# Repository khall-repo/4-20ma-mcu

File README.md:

# 4-20ma-mcu
0-5v to 4-20mA conversion using ATTINY84 and a LM324

This project is just to edify myself on making a PCB and having it fabricated.

Needed to build this project:<br/>
gcc-avr  - GNU C compiler (cross compiler for avr)<br/>
avr-libc - Standard C library for Atmel AVR development<br/>
avrdude  - software for programming Atmel AVR microcontrollers<br/>

Make:<br/>
make           - will compile and link only.<br/>
make flash     - will compile, link, and then program flash memory.<br/>
make fuse      - will compile, link, and then program fuses.<br/>
make program   - will compile, link, program fuses, and then program flash memory.<br/>

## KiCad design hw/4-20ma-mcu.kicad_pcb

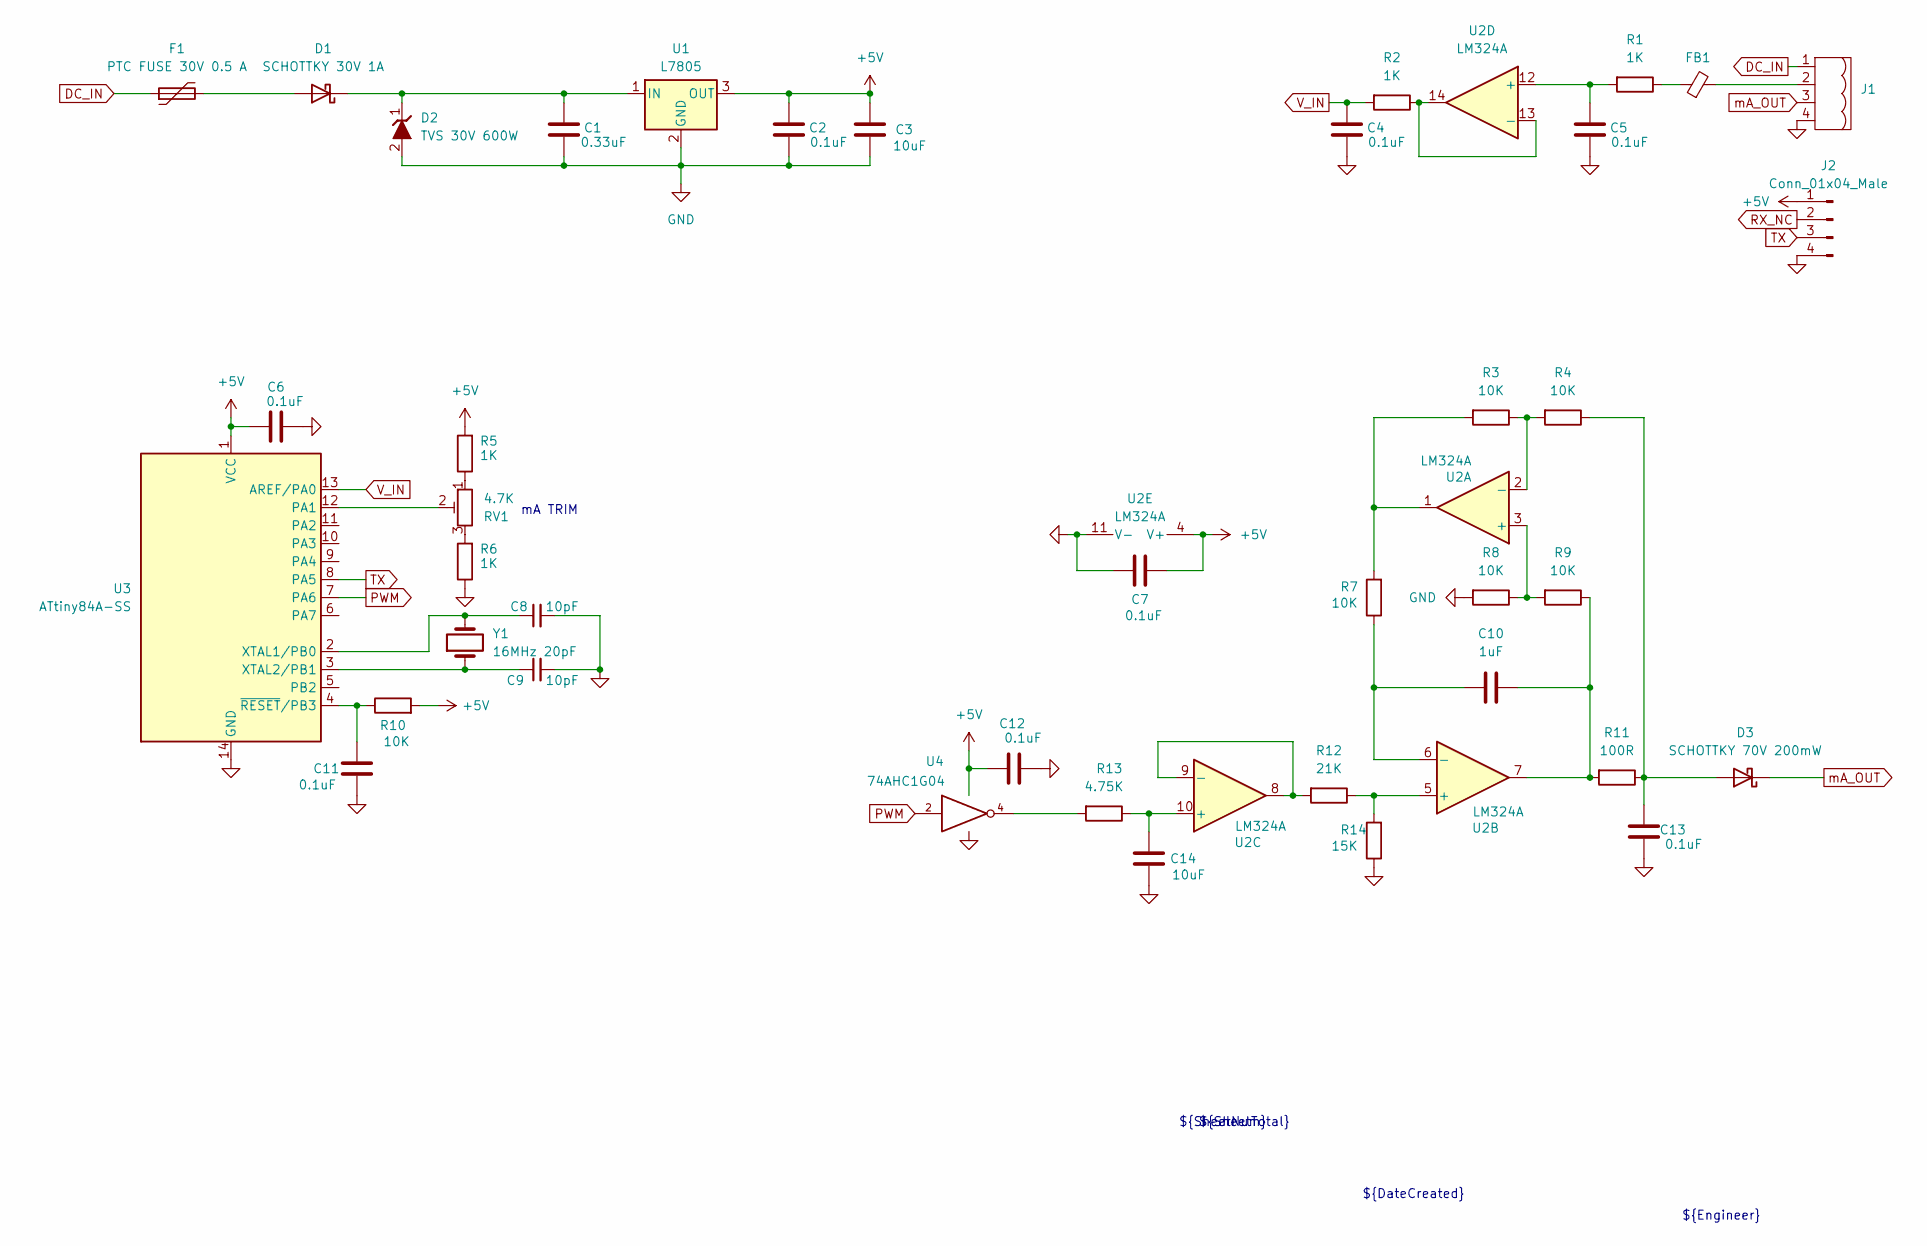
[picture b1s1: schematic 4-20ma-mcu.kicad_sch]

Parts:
C1: 0.33uF; C_0805_2012Metric
C2, C4, C5, C6, C7, C11, C12, C13: 0.1uF; C_0805_2012Metric
C3, C14: 10uF; C_1206_3216Metric
C8, C9: 10pF; C_0603_1608Metric
C10: 1uF; C_0805_2012Metric
D1: SCHOTTKY 30V 1A; D_SMB
D2: TVS 30V 600W; D_SMB
D3: SCHOTTKY 70V 200mW; D_SMB
F1: PTC FUSE 30V 0.5 A; Fuse_1812_4532Metric
FB1: 150 ohm @ 100 MHz 4LN; R_0805_2012Metric
J1: TerminalBlock_Phoenix_MKDS-1,5-4-5.08_1x04_P5.08mm_Horizont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
J2: Conn_01x04_Male; PinHeader_1x04_P2.54mm_Vertical
R1, R2, R5, R6: 1K; R_0805_2012Metric
R3, R4, R7, R8, R9, R10: 10K; R_0805_2012Metric
R11: 100R; R_0805_2012Metric
R12: 21K; R_0805_2012Metric
R13: 4.75K; R_0805_2012Metric
R14: 15K; R_0805_2012Metric
RV1: 4.7K; Potentiometer_Bourns_TC33X_Vertical
U1: L7805; TO-252-2
U2: LM324A; SOIC-14_3.9x8.7mm_P1.27mm
U3: ATtiny84A-SS; SOIC-14_3.9x8.7mm_P1.27mm
U4: 74AHC1G04; SOT-23-5
Y1: 16MHz 20pF; Crystal_SMD_HC49-SD

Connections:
+5V: C2.1, C3.1, C6.2, C7.1, C12.2, J2.1, R5.2, R10.2, U1.3 (OUT), U2.4 (V+), U3.1 (VCC), U4.5 (VCC)
DC_IN: F1.1, J1.1
GND: C1.2, C2.2, C3.2, C4.2, C5.2, C6.1, C7.2, C8.2, C9.2, C11.2, C12.1, C13.2, C14.2, D2.2, J1.4, J2.4, R6.1, R8.2, R14.1, U1.2 (GND), U2.11 (V-), U3.14 (GND), U4.3 (GND)
unnamed: C10.1, R9.1, R11.2, U2.7
unnamed: D1.2 (A), F1.2
unnamed: C1.1, D1.1 (K), D2.1, U1.1 (IN)
unnamed: C13.1, D3.2 (A), R4.1, R11.1
unnamed: FB1.1, R1.1
unnamed: FB1.2, J1.2
unnamed: R3.2, R7.2, U2.1
unnamed: R5.1, RV1.1
unnamed: R6.2, RV1.3
unnamed: R13.2, U4.4
unnamed: R8.1, R9.2, U2.3 (+)
unnamed: R3.1, R4.2, U2.2 (-)
unnamed: R12.1, R14.2, U2.5 (+)
unnamed: C10.2, R7.1, U2.6 (-)
unnamed: C14.1, R13.1, U2.10 (+)
unnamed: R12.2, U2.8, U2.9 (-)
unnamed: C5.1, R1.2, U2.12 (+)
unnamed: R2.1, U2.13 (-), U2.14
unnamed: RV1.2, U3.12 (PA1)
unnamed: C8.1, U3.2 (XTAL1/PB0), Y1.2
unnamed: C9.1, U3.3 (XTAL2/PB1), Y1.1
unnamed: C11.1, R10.1, U3.4 (~RESET/PB3)
PWM: U3.7 (PA6), U4.2
RX_NC: J2.2
TX: J2.3, U3.8 (PA5)
V_IN: C4.1, R2.2, U3.13 (AREF/PA0)
mA_OUT: D3.1 (K), J1.3

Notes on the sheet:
${Engineer}
${DateCreated}
${Revision}
${Title}
${SheetNum}
mA TRIM
${SheetTotal}

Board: 2 copper layers, 41 parts (0 on the bottom side), 29 nets, no tracks yet.

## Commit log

2025-02-21 dev update 022125-0
2025-02-22 dev update 022125-1
2025-02-22 dev update 022225-0
2025-02-22 dev update 022225-1
2025-02-23 dev update 022325-0
2025-03-05 dev update 030425
2025-03-05 030525
2025-03-06 dev update 030525-1
2025-03-06 dev update 030625-0
2025-03-07 dev update 030725-0
2025-03-08 dev update 030725=1
2025-03-11 dev update 031125-0
